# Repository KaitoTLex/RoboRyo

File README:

This is the Robo Ryo Repository

The RoboRyo is a more redundant clone of National Intstrument's RoboRio. It provides long range controls and less BS compared to the FRC legal RoboRio. The upside of RoboRyo is that there are more configurable ports compared to the real RoboRyo and it also includes quality of Life features that the real RoboRio dosen't have. 

This document gives you an overview of the RoboRyo repository and how it works 

Contributers

The RoboRyo PCB is designed by KaitoTLex(Ren Lin)
The RoboRyo Code is developed by Nichloas Luo

This project is licened under the MIT License

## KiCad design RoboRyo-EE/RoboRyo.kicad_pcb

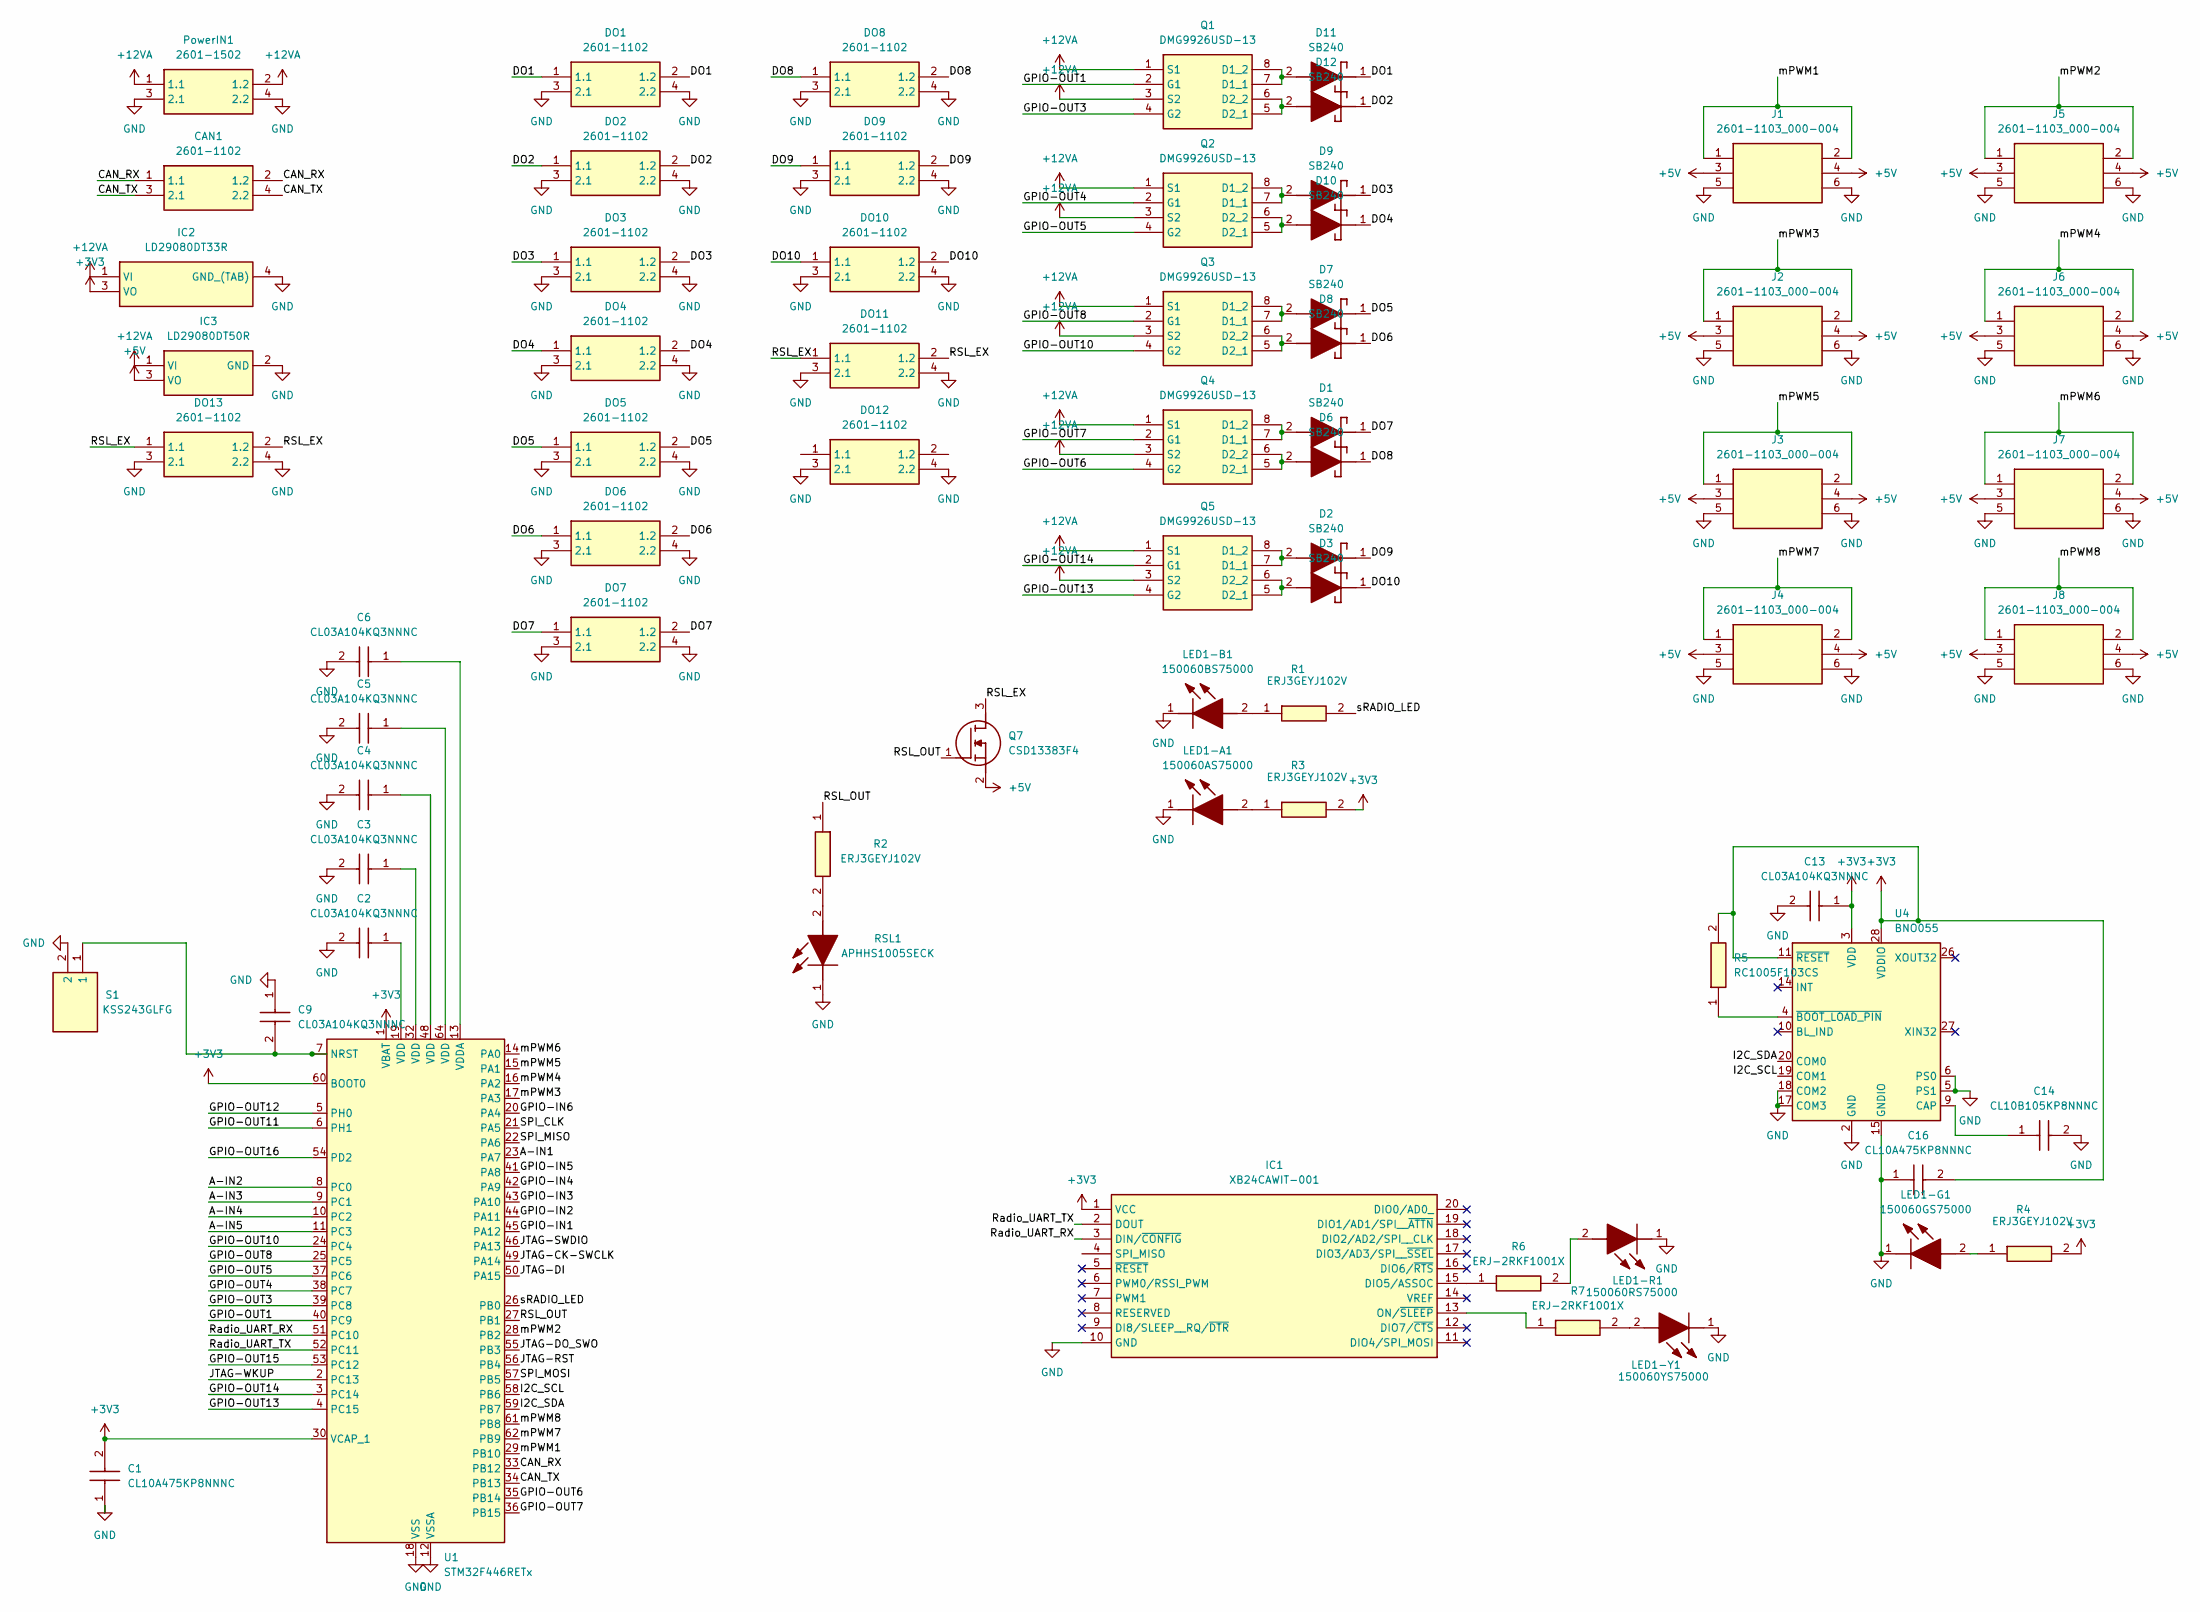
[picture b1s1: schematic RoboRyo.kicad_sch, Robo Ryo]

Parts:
C1, C16: CL10A475KP8NNNC; CAPC1608X90N; Manufacturer_Part_Number CL10A475KP8NNNC; Mouser Part Number 187-CL10A475KP8NNNC
C2, C3, C4, C5, C6, C9, C13: CL03A104KQ3NNNC; CAPC0603X33N; Manufacturer_Part_Number CL03A104KQ3NNNC; Mouser Part Number 187-CL03A104KQ3NNNC
C14: CL10B105KP8NNNC; CAPC1608X90N; Manufacturer_Part_Number CL10B105KP8NNNC; Mouser Part Number 187-CL10B105KP8NNNC
CAN1: 2601-1102; 26011102; Manufacturer_Part_Number 2601-1102
D1, D2, D3, D6, D7, D8, D9, D10, D11, D12: SB240; DIOAD1910W86L670D310; Manufacturer_Part_Number SB240
DO1, DO2, DO3, DO4, DO5, DO6, DO7, DO8, DO9, DO10, DO11, DO12, DO13: 2601-1102; 26011102; Manufacturer_Part_Number 2601-1102
IC1: XB24CAWIT-001; XB24CAWIT001; Mouser Part Number 888-XB24CAWIT-001
IC2: LD29080DT33R; TO228P972X240-3N; Mouser Part Number 511-LD29080DT33R
IC3: LD29080DT50R; Manufacturer_Part_Number LD29080DT50R; Mouser Part Number 511-LD29080DT50R
J1, J2, J3, J4, J5, J6, J7, J8: 2601-1103_000-004; 26011103; Manufacturer_Part_Number 2601-1103/000-004
LED1-A1: 150060AS75000; LEDC1608X80N; Manufacturer_Part_Number 150060AS75000; Mouser Part Number 710-150060AS75000
LED1-B1: 150060BS75000; LEDC1608X80N; Manufacturer_Part_Number 150060BS75000; Mouser Part Number 710-150060BS75000
LED1-G1: 150060GS75000; LEDC1608X80N; Manufacturer_Part_Number 150060GS75000; Mouser Part Number 710-150060GS75000
LED1-R1: 150060RS75000; LEDC1608X80N; Manufacturer_Part_Number 150060RS75000; Mouser Part Number 710-150060RS75000
LED1-Y1: 150060YS75000; LEDC1608X80N; Manufacturer_Part_Number 150060YS75000; Mouser Part Number 710-150060YS75000
PowerIN1: 2601-1502; 26011502; Manufacturer_Part_Number 2601-1502
Q1, Q2, Q3, Q4, Q5: DMG9926USD-13; SOIC127P600X175-8N; Mouser Part Number 621-DMG9926USD-13
Q7: CSD13383F4; Manufacturer_Part_Number CSD13383F4; Mouser Part Number 595-CSD13383F4
R1, R2, R3, R4: ERJ3GEYJ102V; ERJ3EKF1000V; Manufacturer_Part_Number ERJ3GEYJ102V; Mouser Part Number 667-ERJ-3GEYJ102V
R5: RC1005F103CS; RESC1005X40N; Manufacturer_Part_Number RC1005F103CS; Mouser Part Number N/A
R6, R7: ERJ-2RKF1001X; ERJ2RKD1004X; Manufacturer_Part_Number ERJ-2RKF1001X; Mouser Part Number 667-ERJ-2RKF1001X
RSL1: APHHS1005SECK; Manufacturer_Part_Number APHHS1005SECK; Mouser Part Number 604-APHHS1005SECK
S1: KSS243GLFG; KSS; Manufacturer_Part_Number KSS243GLFG; Mouser Part Number 611-KSS243GLFG
U1: STM32F446RETx; LQFP-64_10x10mm_P0.5mm
U4: BNO055; LGA-28_5.2x3.8mm_P0.5mm

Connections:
+3V3: C1.2, C13.1, C16.2, IC1.1 (VCC), IC2.3 (VO), R3.2, R4.2, R5.2, U1.1 (VBAT), U1.30 (VCAP_1), U1.60 (BOOT0), U4.3 (VDD), U4.11 (~RESET), U4.28 (VDDIO)
+5V: IC3.3 (VO), J1.3 (2.1), J1.4 (2.2), J2.3 (2.1), J2.4 (2.2), J3.3 (2.1), J3.4 (2.2), J4.3 (2.1), J4.4 (2.2), J5.3 (2.1), J5.4 (2.2), J6.3 (2.1), J6.4 (2.2), J7.3 (2.1), J7.4 (2.2), J8.3 (2.1), J8.4 (2.2), Q7.2 (S)
+12VA: IC2.1 (VI), IC3.1 (VI), PowerIN1.1 (1.1), PowerIN1.2 (1.2), Q1.1 (S1), Q1.3 (S2), Q2.1 (S1), Q2.3 (S2), Q3.1 (S1), Q3.3 (S2), Q4.1 (S1), Q4.3 (S2), Q5.1 (S1), Q5.3 (S2)
/A-IN1: U1.23 (PA7)
/A-IN2: U1.8 (PC0)
/A-IN3: U1.9 (PC1)
/A-IN4: U1.10 (PC2)
/A-IN5: U1.11 (PC3)
/CAN_RX: CAN1.1 (1.1), CAN1.2 (1.2), U1.33 (PB12)
/CAN_TX: CAN1.3 (2.1), CAN1.4 (2.2), U1.34 (PB13)
/DO1: D11.1 (K), DO1.1 (1.1), DO1.2 (1.2)
/DO2: D12.1 (K), DO2.1 (1.1), DO2.2 (1.2)
/DO3: D9.1 (K), DO3.1 (1.1), DO3.2 (1.2)
/DO4: D10.1 (K), DO4.1 (1.1), DO4.2 (1.2)
/DO5: D7.1 (K), DO5.1 (1.1), DO5.2 (1.2)
/DO6: D8.1 (K), DO6.1 (1.1), DO6.2 (1.2)
/DO7: D1.1 (K), DO7.1 (1.1), DO7.2 (1.2)
/DO8: D6.1 (K), DO8.1 (1.1), DO8.2 (1.2)
/DO9: D2.1 (K), DO9.1 (1.1), DO9.2 (1.2)
/DO10: D3.1 (K), DO10.1 (1.1), DO10.2 (1.2)
/GPIO-IN1: U1.45 (PA12)
/GPIO-IN2: U1.44 (PA11)
/GPIO-IN3: U1.43 (PA10)
/GPIO-IN4: U1.42 (PA9)
/GPIO-IN5: U1.41 (PA8)
/GPIO-IN6: U1.20 (PA4)
/GPIO-OUT1: Q1.2 (G1), U1.40 (PC9)
/GPIO-OUT3: Q1.4 (G2), U1.39 (PC8)
/GPIO-OUT4: Q2.2 (G1), U1.38 (PC7)
/GPIO-OUT5: Q2.4 (G2), U1.37 (PC6)
/GPIO-OUT6: Q4.4 (G2), U1.35 (PB14)
/GPIO-OUT7: Q4.2 (G1), U1.36 (PB15)
/GPIO-OUT8: Q3.2 (G1), U1.25 (PC5)
/GPIO-OUT10: Q3.4 (G2), U1.24 (PC4)
/GPIO-OUT11: U1.6 (PH1)
/GPIO-OUT12: U1.5 (PH0)
/GPIO-OUT13: Q5.4 (G2), U1.4 (PC15)
/GPIO-OUT14: Q5.2 (G1), U1.3 (PC14)
/GPIO-OUT15: U1.53 (PC12)
/GPIO-OUT16: U1.54 (PD2)
/I2C_SCL: U1.58 (PB6), U4.19 (COM1)
/I2C_SDA: U1.59 (PB7), U4.20 (COM0)
/JTAG-CK-SWCLK: U1.49 (PA14)
/JTAG-DI: U1.50 (PA15)
/JTAG-DO_SWO: U1.55 (PB3)
/JTAG-RST: U1.56 (PB4)
/JTAG-SWDIO: U1.46 (PA13)
/JTAG-WKUP: U1.2 (PC13)
/RSL_EX: DO11.1 (1.1), DO11.2 (1.2), DO13.1 (1.1), DO13.2 (1.2), Q7.3 (D)
/RSL_OUT: Q7.1 (G), R2.1, U1.27 (PB1)
/Radio_UART_RX: IC1.3 (DIN/~CONFIG), U1.51 (PC10)
/Radio_UART_TX: IC1.2 (DOUT), U1.52 (PC11)
/SPI_CLK: U1.21 (PA5)
/SPI_MISO: U1.22 (PA6)
/SPI_MOSI: U1.57 (PB5)
/mPWM1: J1.1 (1.1), J1.2 (1.2), U1.29 (PB10)
/mPWM2: J5.1 (1.1), J5.2 (1.2), U1.28 (PB2)
/mPWM3: J2.1 (1.1), J2.2 (1.2), U1.17 (PA3)
/mPWM4: J6.1 (1.1), J6.2 (1.2), U1.16 (PA2)
/mPWM5: J3.1 (1.1), J3.2 (1.2), U1.15 (PA1)
/mPWM6: J7.1 (1.1), J7.2 (1.2), U1.14 (PA0)
/mPWM7: J4.1 (1.1), J4.2 (1.2), U1.62 (PB9)
/mPWM8: J8.1 (1.1), J8.2 (1.2), U1.61 (PB8)
/sRADIO_LED: R1.2, U1.26 (PB0)
GND: C1.1, C2.2, C3.2, C4.2, C5.2, C6.2, C9.1, C13.2, C14.2, C16.1, DO1.3 (2.1), DO1.4 (2.2), DO2.3 (2.1), DO2.4 (2.2), DO3.3 (2.1), DO3.4 (2.2), DO4.3 (2.1), DO4.4 (2.2), DO5.3 (2.1), DO5.4 (2.2), DO6.3 (2.1), DO6.4 (2.2), DO7.3 (2.1), DO7.4 (2.2), DO8.3 (2.1), DO8.4 (2.2), DO9.3 (2.1), DO9.4 (2.2), DO10.3 (2.1), DO10.4 (2.2), DO11.3 (2.1), DO11.4 (2.2), DO12.3 (2.1), DO12.4 (2.2), DO13.3 (2.1), DO13.4 (2.2), IC1.10 (GND), IC2.4 (GND_(TAB)), IC3.2 (GND), J1.5 (3.1), J1.6 (3.2), J2.5 (3.1), J2.6 (3.2), J3.5 (3.1), J3.6 (3.2), J4.5 (3.1), J4.6 (3.2), J5.5 (3.1), J5.6 (3.2), J6.5 (3.1), J6.6 (3.2), J7.5 (3.1), J7.6 (3.2), J8.5 (3.1), J8.6 (3.2), LED1-A1.1 (K), LED1-B1.1 (K), LED1-G1.1 (K), LED1-R1.1 (K), LED1-Y1.1 (K), PowerIN1.3 (2.1), PowerIN1.4 (2.2), RSL1.1 (K), S1.2, U1.12 (VSSA), U1.18 (VSS), U1.31 (VSS), U1.47 (VSS), U1.63 (VSS), U4.2 (GND), U4.5 (PS1), U4.6 (PS0), U4.15 (GNDIO), U4.16 (GNDIO), U4.17 (COM3), U4.18 (COM2), U4.25 (GNDIO)
unnamed: C2.1, U1.19 (VDD)
unnamed: C3.1, U1.32 (VDD)
unnamed: C4.1, U1.48 (VDD)
unnamed: C5.1, U1.64 (VDD)
unnamed: D1.2 (A), Q4.7 (D1_1), Q4.8 (D1_2)
unnamed: D2.2 (A), Q5.7 (D1_1), Q5.8 (D1_2)
unnamed: D3.2 (A), Q5.5 (D2_1), Q5.6 (D2_2)
unnamed: D6.2 (A), Q4.5 (D2_1), Q4.6 (D2_2)
unnamed: D7.2 (A), Q3.7 (D1_1), Q3.8 (D1_2)
unnamed: D8.2 (A), Q3.5 (D2_1), Q3.6 (D2_2)
unnamed: D9.2 (A), Q2.7 (D1_1), Q2.8 (D1_2)
unnamed: D10.2 (A), Q2.5 (D2_1), Q2.6 (D2_2)
unnamed: D11.2 (A), Q1.7 (D1_1), Q1.8 (D1_2)
unnamed: D12.2 (A), Q1.5 (D2_1), Q1.6 (D2_2)
unnamed: IC1.15 (DIO5/ASSOC), R6.1
unnamed: IC1.13 (ON/~SLEEP), R7.1
unnamed: LED1-A1.2 (A), R3.1
unnamed: LED1-B1.2 (A), R1.1
unnamed: LED1-G1.2 (A), R4.1
unnamed: LED1-R1.2 (A), R6.2
unnamed: LED1-Y1.2 (A), R7.2
unnamed: R2.2, RSL1.2 (A)
unnamed: C9.2, S1.1, U1.7 (NRST)
unnamed: C6.1, U1.13 (VDDA)
unnamed: C14.1, U4.9 (CAP)
unnamed: R5.1, U4.4 (~BOOT_LOAD_PIN)

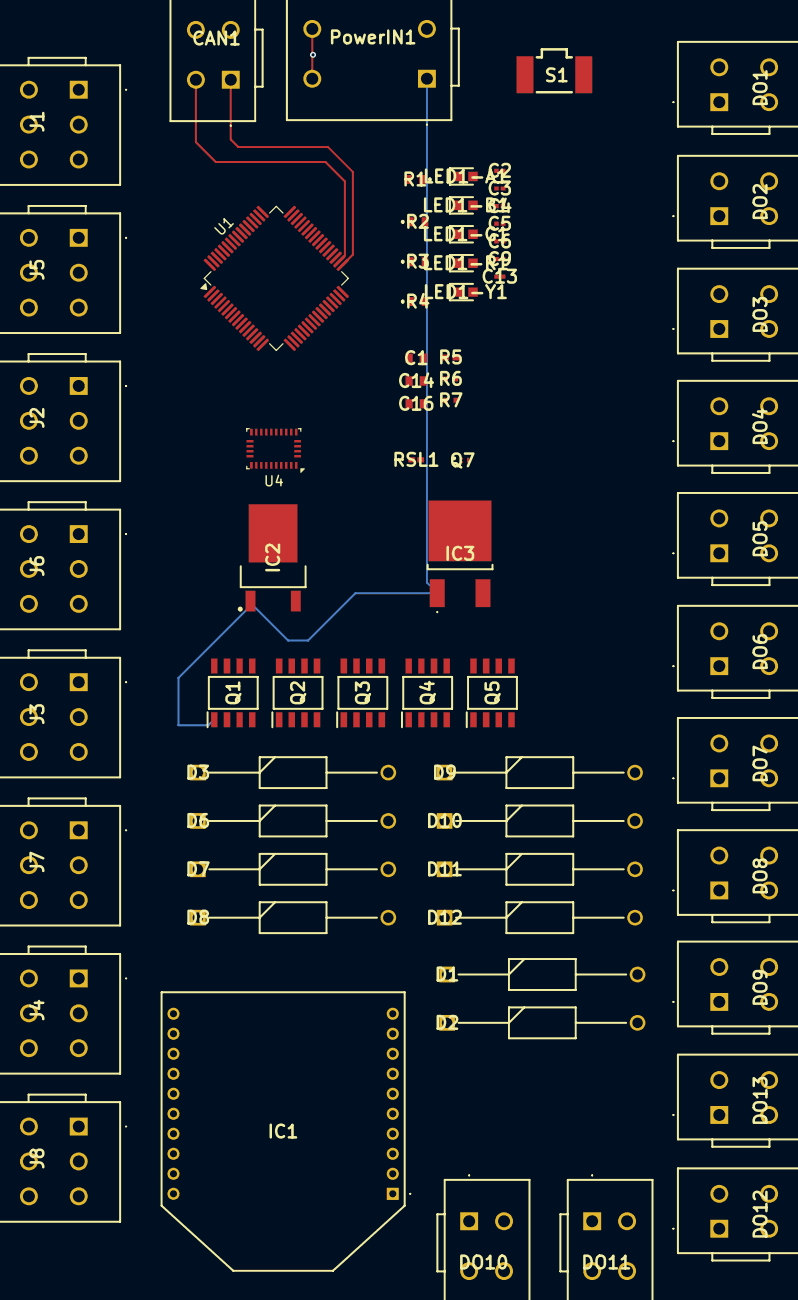
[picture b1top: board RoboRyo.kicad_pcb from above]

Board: 4 copper layers, 68 parts (0 on the bottom side), 67 nets.

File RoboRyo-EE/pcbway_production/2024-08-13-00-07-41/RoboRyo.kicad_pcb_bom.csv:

Designator,Quantity,Value,Footprint,Package,MPN,DNP,Mount_Type,Description,Height,Manufacturer_Name,Mouser Part Number,Mouser Price/Stock,Arrow Part Number,Arrow Price/Stock
"C1, C16",2,CL10A475KP8NNNC,CAPC1608X90N,,CL10A475KP8NNNC,,smt,Multilayer Ceramic Capacitors MLCC - SMD/SMT,0.9,SAMSUNG,187-CL10A475KP8NNNC,https://www.mouser.co.uk/ProductDetail/Samsung-Electro-Mecha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,CL10A475KP8NNNC,https://www.arrow.com/en/products/cl10a475kp8nnnc/samsung-el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
"C13, C2, C3, C4, C5, C6, C9",7,CL03A104KQ3NNNC,CAPC0603X33N,,CL03A104KQ3NNNC,,smt,"Samsung Electro-Mechanics 0201 CL 100nF Ceramic Multilayer Capacitor, 6.3 V, +85C, X5R Dielectric, +/-10% SMD",0.33,SAMSUNG,187-CL03A104KQ3NNNC,https://www.mouser.co.uk/ProductDetail/Samsung-Electro-Mecha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,CL03A104KQ3NNNC,https://www.arrow.com/en/products/cl03a104kq3nnnc/samsung-el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
C14,1,CL10B105KP8NNNC,CAPC1608X90N,,CL10B105KP8NNNC,,smt,1F +/-10% 10V Ceramic Capacitor X7R 0603 (1608 Metric),0.9,SAMSUNG,187-CL10B105KP8NNNC,https://www.mouser.co.uk/ProductDetail/Samsung-Electro-Mecha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,CL10B105KP8NNNC,https://www.arrow.com/en/products/cl10b105kp8nnnc/samsung-el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
"CAN1, DO1, DO10, DO11, DO12, DO13, DO2, DO3, DO4, DO5, DO6, DO7, DO8, DO9",14,2601-1102,26011102,,2601-1102,,tht,"PCB terminal block; lever; 1.5 mm; Pin spacing 3.5 mm; 2-pole; Push-in CAGE CLAMP; 1,50 mm; gray",12.75,Wago,,,,
"D1, D10, D11, D12, D2, D3, D6, D7, D8, D9",10,SB240,DIOAD1910W86L670D310,,SB240,,tht,"Power Schottky (IF1A) - SB240 , Standard, 40V, 2A, DO-15",,PANJIT,,,,
IC1,1,XB24CAWIT-001,XB24CAWIT001,,XB24CAWIT-001,,tht,"802.15.4 Transceiver Module 2.4GHz Integrated, Wire Antenna Through Hole",29.845,DIGI,888-XB24CAWIT-001,https://www.mouser.co.uk/ProductDetail/DIGI/XB24CAWIT-001?qs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,,
IC2,1,LD29080DT33R,TO228P972X240-3N,,LD29080DT33R,,smt,"LD29080DT33R, Low Dropout Voltage Regulator, 0.8A, 3.3 V +/-1%, 2.5  13 Vin, 3-Pin DPAK",2.4,STMicroelectronics,511-LD29080DT33R,https://www.mouser.co.uk/ProductDetail/STMicroelectronics/LD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,,
IC3,1,LD29080DT50R,LD29080DT50R,,LD29080DT50R,,smt,800 mA fixed and adjustable output very low drop voltage regulator,2.63,STMicroelectronics,511-LD29080DT50R,https://www.mouser.co.uk/ProductDetail/STMicroelectronics/LD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,LD29080DT50R,https://www.arrow.com/en/products/ld29080dt50r/stmicroelectr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
"J1, J2, J3, J4, J5, J6, J7, J8",8,2601-1103_000-004,26011103,,2601-1103/000-004,,tht,"PCB terminal block; lever; 1.5 mm; Pin spacing 3.5 mm; 3-pole; Push-in CAGE CLAMP; 1,50 mm; gray",12.75,Wago,,,,
LED1-A1,1,150060AS75000,LEDC1608X80N,,150060AS75000,,smt,"2.4 V Amber LED 1608 (0603)  SMD, Wurth Elektronik WL-SMCW 150060AS75000",0.8,Wurth Elektronik,710-150060AS75000,https://www.mouser.co.uk/ProductDetail/Wurth-Elektronik/1500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,,
LED1-B1,1,150060BS75000,LEDC1608X80N,,150060BS75000,,smt,"LED,Wurth Elektronik,150060BS75000 Wurth Elektronik 150060BS75000, WL-SMCW Series Blue LED, 470 nm 1608 (0603) Clear, Rectangle Lens SMD package",0.8,Wurth Elektronik,710-150060BS75000,https://www.mouser.co.uk/ProductDetail/Wurth-Elektronik/1500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,,
LED1-G1,1,150060GS75000,LEDC1608X80N,,150060GS75000,,smt,"Wurth Elektronik WL-SMCW 520 nm Green LED, 1608 (0603) Clear SMD package",0.8,Wurth Elektronik,710-150060GS75000,https://www.mouser.co.uk/ProductDetail/Wurth-Elektronik/1500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,,
LED1-R1,1,150060RS75000,LEDC1608X80N,,150060RS75000,,smt,"WURTH ELEKTRONIK - 150060RS75000 - LED, 0603, RED, 250MCD, 625NM",0.8,Wurth Elektronik,710-150060RS75000,https://www.mouser.co.uk/ProductDetail/Wurth-Elektronik/1500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,,
LED1-Y1,1,150060YS75000,LEDC1608X80N,,150060YS75000,,smt,"LED,Wurth Elektronik,150060YS75000 Wurth Elektronik 150060YS75000, WL-SMCW Series Yellow LED, 590 nm, 1608 (0603) Clear, Rectangle Lens SMD Package",0.8,Wurth Elektronik,710-150060YS75000,https://www.mouser.co.uk/ProductDetail/Wurth-Elektronik/1500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,,
PowerIN1,1,2601-1502,26011502,,2601-1502,,tht,PCB terminal block; lever; 1.5 mm; Pin spacing 11.5 mm; 2-pole; Push-in CAGE CLAMP,12.75,Wago,,,,
"Q1, Q2, Q3, Q4, Q5",5,DMG9926USD-13,SOIC127P600X175-8N,,DMG9926USD-13,,smt,"Diodes Inc DMG9926USD-13 Dual N-channel MOSFET Transistor, 8 A, 20 V, 8-Pin SOP",1.75,Diodes Incorporated,621-DMG9926USD-13,https://www.mouser.co.uk/ProductDetail/Diodes-Incorporated/D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,,
Q7,1,CSD13383F4,CSD13383F4,,CSD13383F4,,smt,"12V, N ch NexFET MOSFET, single LGA 1.0 x 0.6mm, 44mOhm",0.35,Texas Instruments,595-CSD13383F4,https://www.mouser.co.uk/ProductDetail/Texas-Instruments/CSD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,CSD13383F4,https://www.arrow.com/en/products/csd13383f4/texas-instrumen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
"R1, R2, R3, R4",4,ERJ3GEYJ102V,ERJ3EKF1000V,,ERJ3GEYJ102V,,smt,Thick Film Resistors - SMD 0603 1Kohms 5% AEC-Q200,0.55,Panasonic,667-ERJ-3GEYJ102V,http://www.mouser.com/Search/ProductDetail.aspx?qs=66DK8nO8g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,,
R5,1,RC1005F103CS,RESC1005X40N,,RC1005F103CS,,smt,Thick Film General Chip Resistor,0.4,SAMSUNG,N/A,https://www.mouser.com/Search/Refine.aspx?Keyword=N%2FA,RC1005F103CS,https://www.arrow.com/en/products/rc1005f103cs/samsung-elect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
"R6, R7",2,ERJ-2RKF1001X,ERJ2RKD1004X,,ERJ-2RKF1001X,,smt,Thick Film Resistors - SMD 0402 1Kohms 1% AEC-Q200,0.4,Panasonic,667-ERJ-2RKF1001X,https://www.mouser.co.uk/ProductDetail/Panasonic/ERJ-2RKF100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,ERJ-2RKF1001X,https://www.arrow.com/en/products/erj-2rkf1001x/panasonic?re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
RSL1,1,APHHS1005SECK,APHHS1005SECK,,APHHS1005SECK,,smt,Standard LEDs - SMD ORANGE WTR CLEAR 160mcd 610nm,0.6,Kingbright,604-APHHS1005SECK,https://www.mouser.co.uk/ProductDetail/Kingbright/APHHS1005S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,APHHS1005SECK,https://www.arrow.com/en/products/aphhs1005seck/kingbright?r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
S1,1,KSS243GLFG,KSS,,KSS243GLFG,,smt,KSS243GLFG (Tactile Switches),,C & K COMPONENTS,611-KSS243GLFG,https://www.mouser.co.uk/ProductDetail/CK/KSS243GLFG?qs=vOd3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,KSS243GLFG,https://www.arrow.com/en/products/kss243glfg/ck
U1,1,STM32F446RETx,LQFP-64_10x10mm_P0.5mm,,,,smt,"STMicroelectronics Arm Cortex-M4 MCU, 512KB flash, 128KB RAM, 180 MHz, 1.8-3.6V, 50 GPIO, LQFP64",,,,,,
U4,1,BNO055,LGA-28_5.2x3.8mm_P0.5mm,,,,smt,"Intelligent 9-axis absolute orientation sensor, LGA-28",,,,,,

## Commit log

2024-04-05 RoboRyo-EE commit
2024-04-09 Added: STM8 Microcontroller and Setup Sch page
2024-04-13 Added parts from previous CAD file
2024-04-13 Added parts from previous CAD file part 2
2024-04-15 updated sch
2024-04-16 added power to STM32F446RETx
2024-04-17 added diodes and the PCB is now solonoid ready
2024-04-18 added connector ports for PWM
2024-04-18 deleted critical power budget vunerability
2024-04-18 Added a RSL for safety :nerd:
2024-04-26 added new components
2024-05-17 added README
2024-07-20 Sch New: IMU, Radio, PowerConfiguration
2024-08-13 Sch Complete, PCB: General Layout complete, wiring left
2024-08-18 Sch Edited: I am stupid, PCB:Pending Completition
